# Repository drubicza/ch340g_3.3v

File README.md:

# 3.3V CH340G
Just a minimalist and functional 3.3V CH340G USB to Serial converter.

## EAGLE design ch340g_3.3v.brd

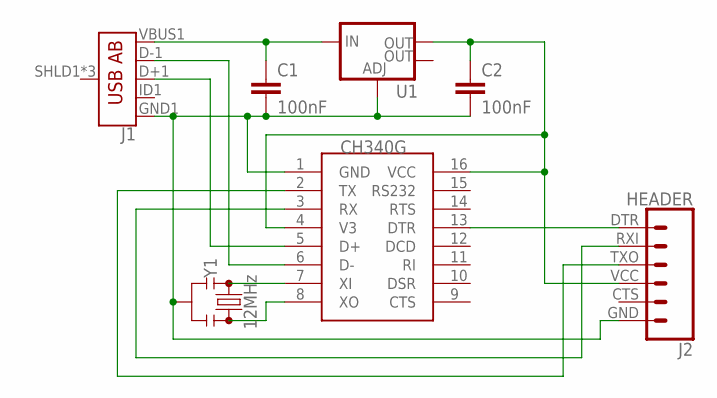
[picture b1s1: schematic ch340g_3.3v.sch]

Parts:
C1, C2: 100nF; 0805
J1: USB_AB_SMT; USB-AB-MICRO-SMD
J2: HEADER; FTDI_BASIC
U1: V_REG_LM1117SOT223; SOT223
U$1: CH340G; SOIC16
Y1: 12MHz; RESONATOR-SMD-3.2X1.3

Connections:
GND: C1.2, C2.2, J1.GND1 (GND), J2.GND (6), U1.1 (ADJ), U$1.1 (GND), Y1.2
unnamed: U$1.7 (XI), Y1.1
unnamed: U$1.8 (XO), Y1.3
unnamed: C1.1, J1.VBUS1 (VBUS), U1.3 (IN)
unnamed: J1.D+1 (D+), U$1.5 (D+)
unnamed: J1.D-1 (D-), U$1.6 (D-)
unnamed: J2.RXI (2), U$1.3 (RX)
unnamed: J2.TXO (3), U$1.2 (TX)
unnamed: C2.1, J2.VCC (4), U1.2 (OUT), U$1.4 (V3), U$1.16 (VCC)
unnamed: J2.DTR (1), U$1.13 (DTR)

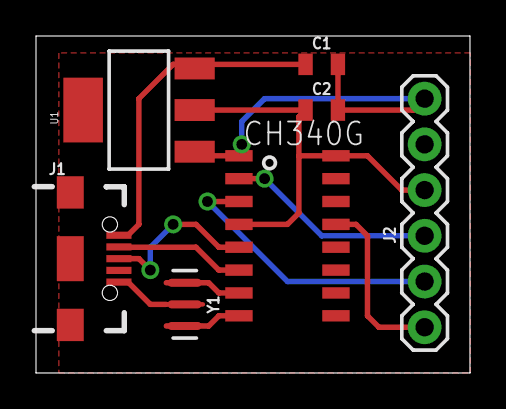
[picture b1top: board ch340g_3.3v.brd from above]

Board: 2 copper layers, 24.1 x 18.7 mm, 7 parts (0 on the bottom side), 10 nets.

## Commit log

2017-03-06 Initial commit :octocat:

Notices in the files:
parts and their libraries:
SparkFun-Capacitors: Licensing: Creative Commons ShareAlike 4.0 International - https://creativecommons.org/licenses/by-sa/4.0
